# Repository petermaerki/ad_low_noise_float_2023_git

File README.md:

# ad_low_noise_float_2023_git

Ad converter hardware connecting to USB. Used to measure low frequency noise.

* [Instructions (PDF)](instructions/20250919b_instructions_ad_low_noise_float_2023.pdf)
* [Labber Driver (git repo)](https://github.com/nanophysics/labber_ad_low_noise_float_2023)

## Relations between the different software packags

```mermaid
architecture-beta
    group hw(cloud)[Hardware]
    group api(cloud)[API]
    group app(cloud)[Application]

    service pcb(internet)[HardwarePcb] in hw
    service decoder(cloud)[Decoder] in api
    service ad(cloud)[Ad] in api
    service pymeas(server)[Pymeas] in app
    service labber(server)[Labber] in app

    ad:T <--> B:pcb
    decoder:L <-- R:ad
    ad:B <-- T:pymeas
    ad:B <-- T:labber
```

* PCB: The hardware (PCB)
  * https://github.com/petermaerki/ad_low_noise_float_2023_git
  * Directory `hardware` KiCad
  * Directory `software/pico` C++

* Decoder: python package: The protocol decoder written in C++/pybind11
  * https://github.com/petermaerki/ad_low_noise_float_2023_git
  * Directory `software/decoder`

* Ad: python package: The logic to communicate with the PCB
  * https://github.com/petermaerki/ad_low_noise_float_2023_git
  * Directory `src/ad_low_noise_float_2023`

* Labber: The Labber driver written in python
  * https://github.com/nanophysics/labber_ad_low_noise_float_2023

* Pymeas: python application
  * https://github.com/nanophysics/pymeas2019_noise

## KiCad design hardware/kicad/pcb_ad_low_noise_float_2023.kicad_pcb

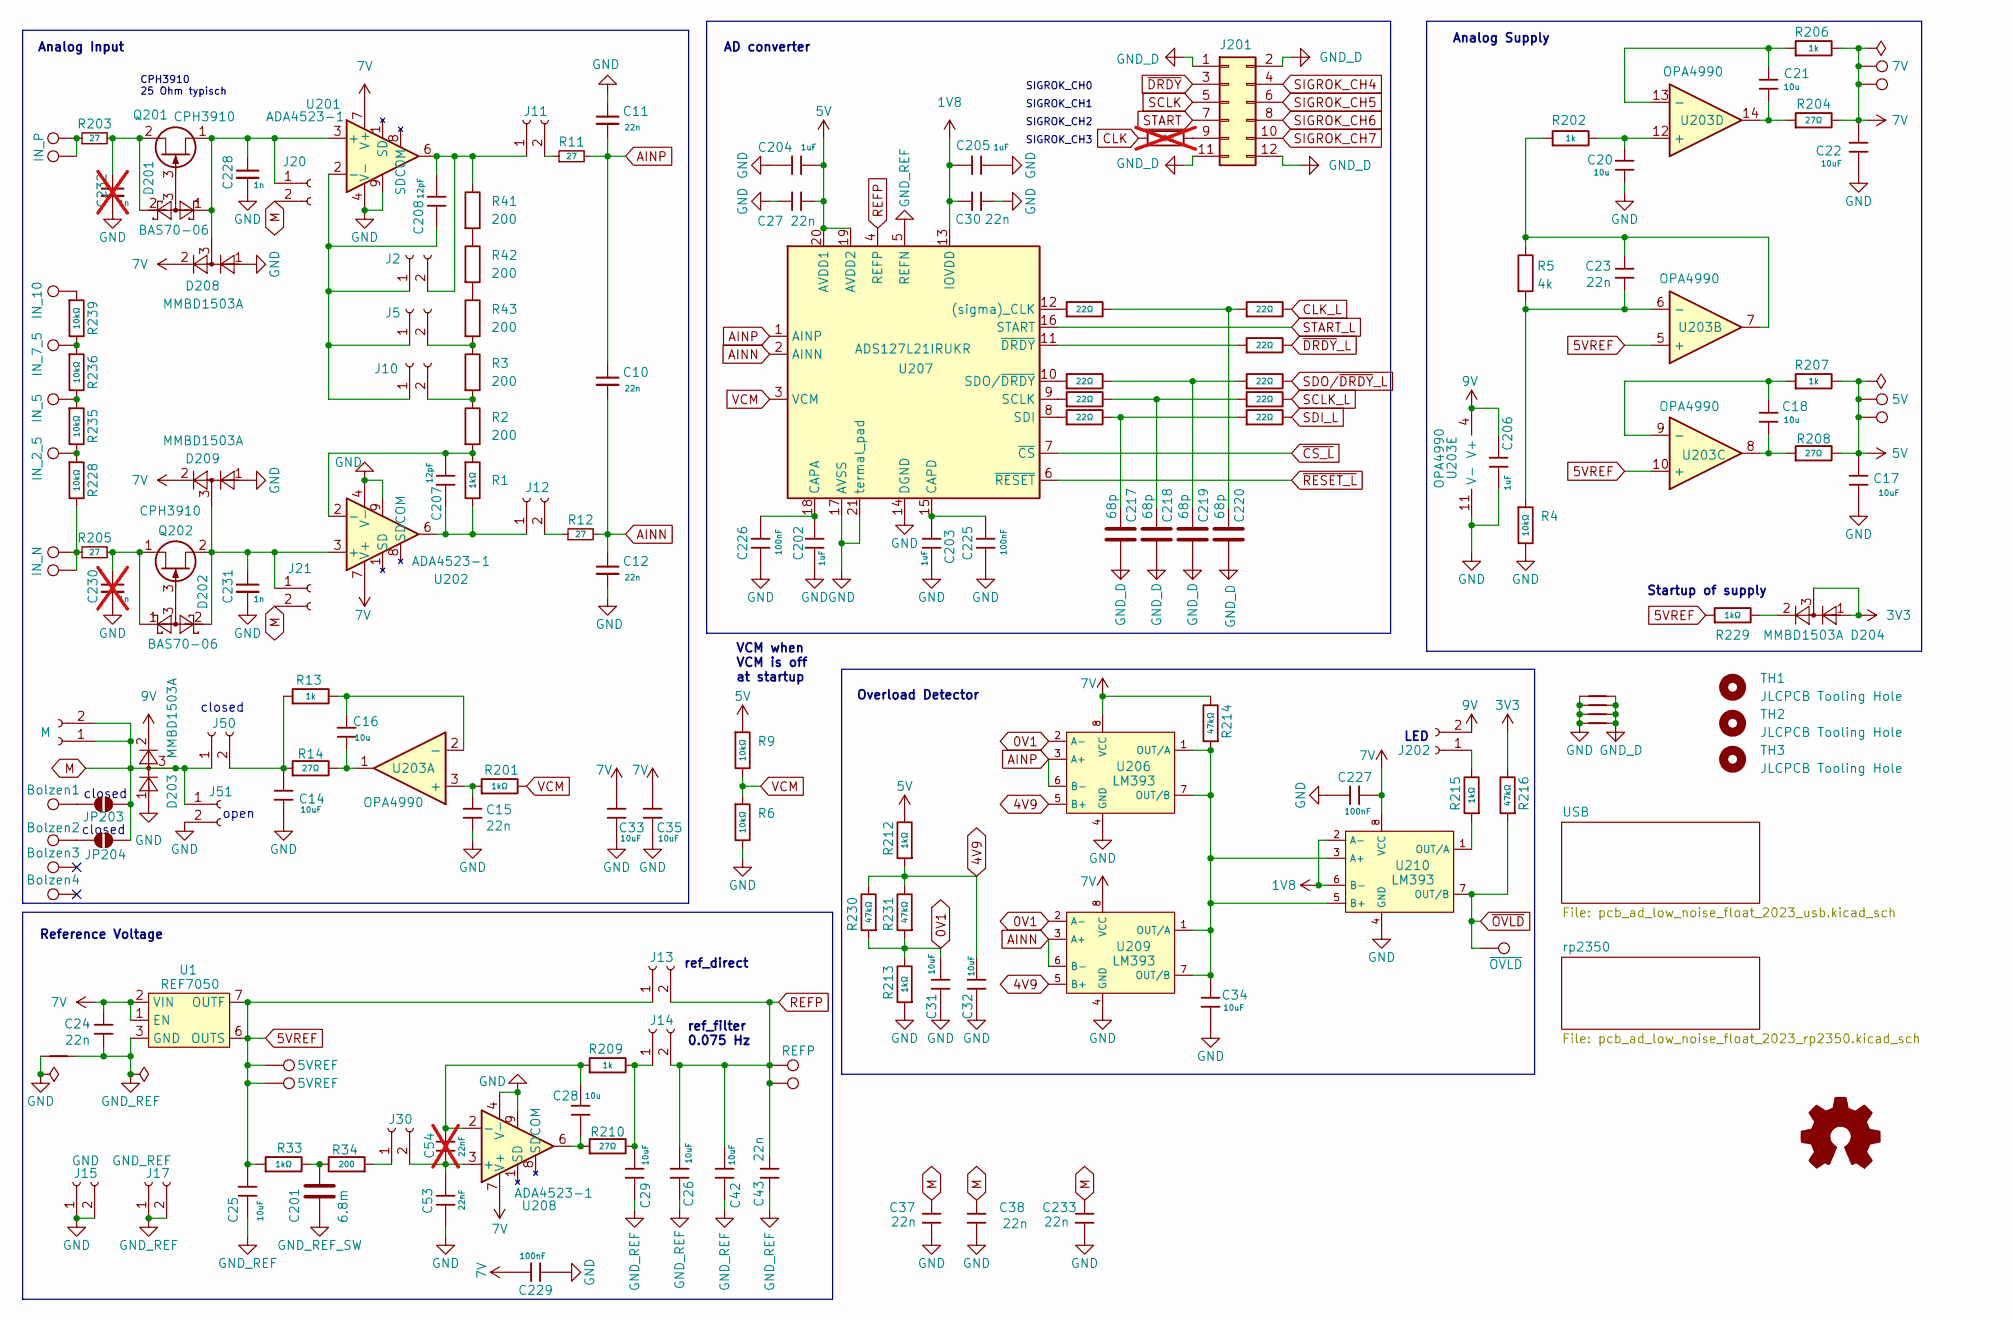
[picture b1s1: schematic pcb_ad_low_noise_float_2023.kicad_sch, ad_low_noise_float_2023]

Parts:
C10, C11, C12: 22n; C_0805; LCSC C77069
C14: 10uF; C_0805; Voltage Rated 50V; Tolerance ±10%; Part GRM21BR61H106KE43L; LCSC C440198
C15, C23, C24, C27, C30, C37, C38, C43, C233: 22n; C_0805; JLC C77069
C16, C18, C20, C21: 10u; C_0805; JLCPCB C440198
C17, C22, C25, C26, C29, C31, C32, C33, C34, C35, C42: 10uF; C_0805; Voltage Rated 50V; Tolerance ±10%; Part GRM21BR61H106KE43L; JLC C440198
C28: 10u; C_0805; Voltage Rated 50V; Tolerance ±10%; Part GRM21BR61H106KE43L; LCSC C440198
C53: 22nF; C_0805; LCSC C77069
C54: 22nF; C_0805; JLC C77069; not fitted
C201: 6.8m; CP_Radial_D18.0mm_P7.50mm_flach_unten
C202, C203, C204, C205, C206: 1uF; C_0805; Voltage Rated 50V; Tolerance ±10%; Part CL21B105KBFNNNE; LCSC C28323
C207, C208: 12pF; C_0805; Voltage Rated 50V; Tolerance ±5%; Part 0805CG120J500NT; LCSC C1792
C217, C218, C219, C220: 68p; C_0402_1005Metric
C225, C226, C227, C229: 100nF; C_0402; Voltage Rated 50V; Tolerance ±10%; Part CL05B104KB54PNC; LCSC C307331
C228, C231: 1n; C_0805; LCSC C46653
C230, C232: 1n; C_0805; LCSC C46653; not fitted
D201, D202: BAS70-06; SOT-23; JLC C22466364
D203, D204, D208, D209: MMBD1503A; SOT-23
IN_N201, IN_N202: IN_N; octoprobe_breakout_PB
IN_N203: IN_2_5; octoprobe_breakout_PB
IN_N204: IN_5; octoprobe_breakout_PB
IN_N205: IN_7_5; octoprobe_breakout_PB
IN_N206: IN_10; octoprobe_breakout_PB
IN_P201, IN_P213: IN_P; octoprobe_breakout_PB
IN_P202, IN_P214: 5V; octoprobe_breakout_PB
IN_P203, IN_P215: 7V; octoprobe_breakout_PB
IN_P206: ~{OVLD}; TestPoint_THTPad_2.0x2.0mm_Drill1.0mm
IN_P208, IN_P212: 5VREF; octoprobe_breakout_PB
IN_P209, IN_P216: REFP; octoprobe_breakout_PB
J2, J5, J10, J11, J12, J13, J14, J20, J21, J30, J50, J51: Conn_01x02_Socket; stiftenleiste_bruecke
J15: GND; stiftenleiste_bruecke
J16: M; stiftenleiste_bruecke
J17: GND_REF; stiftenleiste_bruecke
J201: Conn_02x06_Odd_Even; PinHeader_2x06_P2.54mm_Vertical
J202: stiftenleiste_bruecke
JP203, JP204: SolderJumper_2_Open; SolderJumper-2_P1.3mm_Open_RoundedPad1.0x1.5mm
Logo_open_hardware101: Logo_Open_Hardware_Small; OSHW-Logo2_9.8x8mm_SilkScreen
NT201, NT202, NT203: NetTie_project; NetTie-2_Peter
NT204: NetTie_project; NetTie-2_Peter_wide_back
NT205: NetTie_project; NetTie-2_SMD_Pad0.5mm
Q201, Q202: CPH3910; SOT-23; JLC C480726
R1, R33, R201, R212, R213, R215, R229: 1kΩ; R_0805; JLC C110774
R2, R3, R41, R42, R43: 200; C_0805_2012Metric_Pad1.18x1.45mm_HandSolder; JLC C218416
R4, R228, R235, R236, R239: 10kΩ; R_0805; JLCPCB C509088
R5: 4k; C_0805_2012Metric_Pad1.18x1.45mm_HandSolder; JLC C2828855
R6, R9: 10kΩ; R_0805; Overload Voltage (Max) 150V; Tolerance ±1%; Part 0805W8F1002T5E; JLC C110775
R11, R12, R203, R205: 27; R_0805; LCSC C17594
R13, R202, R206, R207, R209: 1k; R_0805; JLC C110774
R14, R204, R208, R210: 27Ω; R_0805; Overload Voltage (Max) 150V; Tolerance ±1%; Part 0805W8F270JT5E; LCSC C17594
R34: 200; R_0805; JLC C218416
R214, R216, R230, R231: 47kΩ; R_0805; Overload Voltage (Max) 150V; Tolerance ±1%; Part 0805W8F4702T5E; LCSC C17713
R221, R222, R223, R224, R225, R226, R234, R237, R238: 22Ω; R_0402; Overload Voltage (Max) 50V; Tolerance ±1%; Part 0402WGF220JTCE; LCSC C25092
R227: 22Ω; R_0402; Overload Voltage (Max) 50V; Tolerance ±1%; Part 0402WGF220JTCE; LCSC C25092; not fitted
TH1, TH2, TH3: JLCPCB Tooling Hole; JLCPCB_ToolingHole
TP201: Bolzen1; distanzbolz_3
TP202: Bolzen2; distanzbolz_3
TP203: Bolzen3; distanzbolz_3
TP204: Bolzen4; distanzbolz_3
U1: REF7050; Analog_LCC-8_5x5mm_P1.27mm; LCSC C6760318
U201, U202, U208: ADA4523-1; LFCSP-8-1EP_3x3mm_P0.5mm_EP1.6x2.34mm_ThermalVias; JLC C4371130
U203: OPA4990; TSSOP-14_4.4x5mm_P0.65mm; JLC C2862600
U206, U209, U210: LM393; SOIC-8_L5.0-W4.0-P1.27-LS6.0-BL; Supply Voltage 2V~36V;1V~18V; Part LM393DR2G; LCSC C7955
U207: ADS127L21IRUKR; WQFN-20-1EP_3x3mm_P0.4mm_EP1.7x1.7mm_ThermalVias; JLC C20606868

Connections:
0V1: C31.1, R213.2, R230.1, R231.1, U206.2 (A-), U209.2 (A-)
1V8: C30.1, C205.2, U207.13 (IOVDD), U210.2 (A-), U210.6 (B-); also elsewhere on the board
3V3: D204.1, D204.3, R216.2; also elsewhere on the board
4V9: C32.1, R212.1, R230.2, R231.2, U206.5 (B+), U209.5 (B+)
5V: C17.1, C27.2, C204.1, IN_P202.1, IN_P214.1, R9.1, R207.2, R208.2, R212.2, U207.19 (AVDD2), U207.20 (AVDD1)
5VREF: C25.1, IN_P208.1, IN_P212.1, J13.1, R33.1, R229.1, U1.6 (OUTS), U1.7 (OUTF), U203.5 (+), U203.10 (+)
7V: C22.1, C24.1, C33.1, C35.1, C227.1, C229.1, D208.2, D209.2, IN_P203.1, IN_P215.1, R204.2, R206.2, R214.2, U1.1 (EN), U1.2 (VIN), U201.7 (V+), U202.7 (V+), U206.8 (VCC), U208.7 (V+), U209.8 (VCC), U210.8 (VCC)
9V: C206.1, D203.2, J202.2, U203.4 (V+); also elsewhere on the board
AINN: C10.2, C12.1, R12.2, U207.2 (AINN), U209.3 (A+), U209.6 (B-)
AINP: C10.1, C11.2, R11.2, U206.3 (A+), U206.6 (B-), U207.1 (AINP)
CLK: R227.1; also elsewhere on the board
CLK_L: R234.2; also elsewhere on the board
GND: C11.1, C12.2, C14.2, C15.2, C17.2, C20.2, C22.2, C27.1, C30.2, C31.2, C32.2, C33.2, C34.2, C35.2, C37.2, C38.2, C53.2, C202.2, C203.2, C204.2, C205.1, C206.2, C225.2, C226.2, C227.2, C228.2, C229.2, C230.2, C231.2, C232.2, C233.2, D203.1, D208.1, D209.1, J15.1, J15.2, J51.2, NT201.1, NT202.1, NT203.1, NT204.1, NT205.1, R4.2, R6.2, R213.1, U201.4 (V-), U201.9, U202.4 (V-), U202.9, U203.11 (V-), U206.4 (GND), U207.14 (DGND), U207.17 (AVSS), U207.21 (termal_pad), U208.4 (V-), U208.9, U209.4 (GND), U210.4 (GND); also elsewhere on the board
GND_D: C217.2, C218.2, C219.2, C220.2, J201.1, J201.2, J201.11, J201.12, NT202.2, NT203.2, NT204.2, NT205.2; also elsewhere on the board
GND_REF: C24.2, C25.2, C26.2, C29.2, C42.2, C43.2, J17.1, J17.2, NT201.2, U1.3 (GND), U1.4 (GND), U1.5 (GND), U1.8 (GND), U207.5 (REFN); also elsewhere on the board
GND_REF_SW: C201.2; also elsewhere on the board
M: C37.1, C38.1, C233.1, D203.3, J16.1, J16.2, J20.2, J21.2, J50.1, J51.1, JP203.2 (B), JP204.2 (B)
unnamed: C16.2, R14.2, U203.1
unnamed: C18.2, R208.1, U203.8
unnamed: C21.2, R204.1, U203.14
unnamed: C23.1, R5.1, R202.1, U203.7
unnamed: C28.2, R210.1, U208.6
unnamed: C201.1, R33.2, R34.1
unnamed: C217.1, R222.2, R226.1
unnamed: C218.1, R225.2, R238.1
unnamed: C219.1, R224.2, R237.1
unnamed: C220.1, R221.2, R234.1
unnamed: D204.2, R229.2
unnamed: IN_N201.1, IN_N202.1, R205.1, R228.2
unnamed: IN_N203.1, R228.1, R235.2
unnamed: IN_N204.1, R235.1, R236.2
unnamed: IN_N205.1, R236.1, R239.2
unnamed: IN_N206.1, R239.1
unnamed: IN_P201.1, IN_P213.1, R203.1
unnamed: J5.2, R3.1, R43.2
unnamed: C208.2, J2.1, J5.1, J10.1, U201.2 (-)
unnamed: J10.2, R2.1, R3.2
unnamed: C208.1, J2.2, J11.1, R41.1, U201.6
unnamed: J11.2, R11.1
unnamed: C207.2, J12.1, R1.2, U202.6
unnamed: J12.2, R12.1
unnamed: C29.1, J14.1, R209.2, R210.2
unnamed: C228.1, D201.1, D208.3, J20.1, Q201.1 (S), U201.3 (+)
unnamed: C231.1, D202.2, D209.3, J21.1, Q202.2 (D), U202.3 (+)
unnamed: J30.1, R34.2
unnamed: C53.1, C54.1, J30.2, U208.3 (+)
unnamed: C14.1, J50.2, R13.1, R14.1
unnamed: J201.9, R227.2
unnamed: J202.1, R215.2
unnamed: JP203.1 (A), TP201.1
unnamed: JP204.1 (A), TP202.1
unnamed: C232.1, D201.2, Q201.2 (D), R203.2
unnamed: D201.3, Q201.3 (G)
unnamed: D202.3, Q202.3 (G)
unnamed: C230.1, D202.1, Q202.1 (S), R205.2
unnamed: R41.2, R42.1
unnamed: R42.2, R43.1
unnamed: C207.1, R1.1, R2.2, U202.2 (-)
unnamed: C15.1, R201.1, U203.3 (+)
unnamed: C16.1, R13.2, U203.2 (-)
unnamed: C23.2, R4.1, R5.2, U203.6 (-)
unnamed: C18.1, R207.1, U203.9 (-)
unnamed: C20.1, R202.2, U203.12 (+)
unnamed: C21.1, R206.1, U203.13 (-)
unnamed: C34.1, R214.1, U206.1 (OUT/A), U206.7 (OUT/B), U209.1 (OUT/A), U209.7 (OUT/B), U210.3 (A+), U210.5 (B+)
unnamed: R221.1, U207.12 ((sigma)_CLK)
unnamed: C202.1, C226.1, U207.18 (CAPA)
unnamed: C203.1, C225.1, U207.15 (CAPD)
unnamed: R225.1, U207.9 (SCLK)
unnamed: R222.1, U207.8 (SDI)
unnamed: R224.1, U207.10 (SDO/~DRDY)
unnamed: R223.1, U207.11 (~DRDY)
unnamed: C28.1, C54.2, R209.1, U208.2 (-)
unnamed: R215.1, U210.1 (OUT/A)
REFP: C26.1, C42.1, C43.1, IN_P209.1, IN_P216.1, J13.2, J14.2, U207.4 (REFP)
SCLK: J201.5; also elsewhere on the board
SCLK_L: R238.2; also elsewhere on the board
SDI_L: R226.2; also elsewhere on the board
SDO/~DRDY_L: R237.2; also elsewhere on the board
SIGROK_CH4: J201.4; also elsewhere on the board
SIGROK_CH5: J201.6; also elsewhere on the board
SIGROK_CH6: J201.8; also elsewhere on the board
SIGROK_CH7: J201.10; also elsewhere on the board
START: J201.7; also elsewhere on the board
START_L: U207.16 (START); also elsewhere on the board
VCM: R6.1, R9.2, R201.2, U207.3 (VCM)
~CS_L: U207.7 (~CS); also elsewhere on the board
~DRDY: J201.3; also elsewhere on the board
~DRDY_L: R223.2; also elsewhere on the board
~OVLD: IN_P206.1, R216.1, U210.7 (OUT/B); also elsewhere on the board
~RESET_L: U207.6 (~RESET); also elsewhere on the board

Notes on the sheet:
SIGROK_CH1
SIGROK_CH2
ref_filter 0.075 Hz
closed
LED
Reference Voltage
Overload Detector
open
Startup of supply
AD converter
CPH3910 25 Ohm typisch
ref_direct
VCM when VCM is off at startup
SIGROK_CH0
Analog Input
SIGROK_CH3
Analog Supply

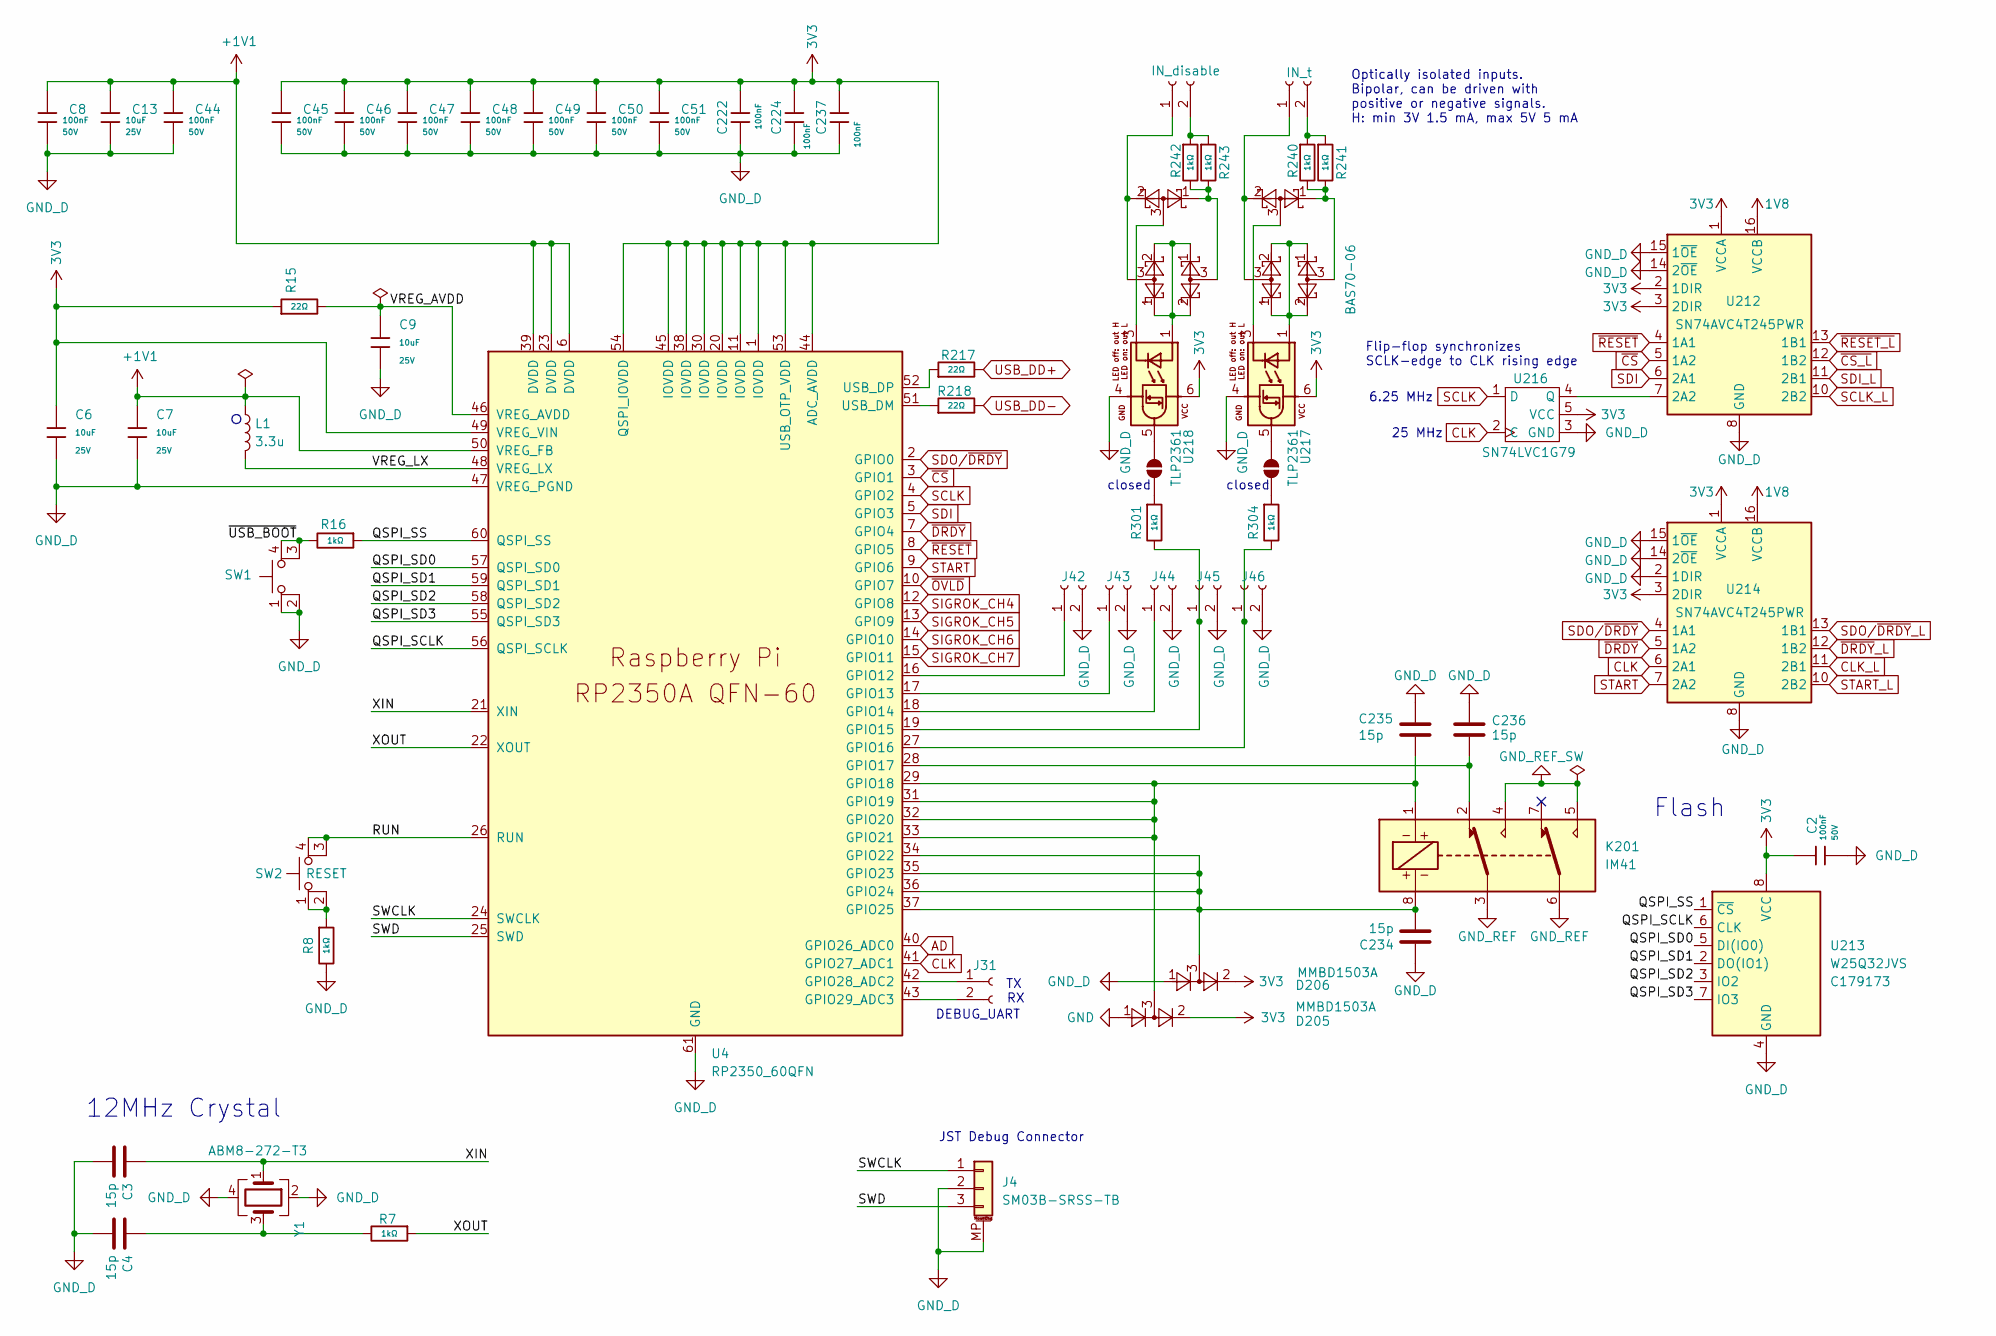
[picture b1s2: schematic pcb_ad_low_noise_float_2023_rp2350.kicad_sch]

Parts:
C2, C8, C44, C45, C46, C47, C48, C49, C50, C51, C222, C224, C237: 100nF; C_0402; Voltage Rated 50V; Tolerance ±10%; Part CL05B104KB54PNC; LCSC C307331
C3, C4, C234, C235, C236: 15p; C_0402_1005Metric
C6, C7, C9, C13: 10uF; C_0603; Voltage Rated 25V; Tolerance ±20%; Part CL10A106MA8NRNC; LCSC C96446
D205, D206: MMBD1503A; SOT-23
D210, D211, D212, D213, D214, D215: BAS70-06; SOT-23; JLC C22466364
J4: SM03B-SRSS-TB; JST_SH_SM03B-SRSS-TB_1x03-1MP_P1.00mm_Horizontal; JLC C160403
J31, J42, J43, J44, J45, J46: Conn_01x02_Socket; stiftenleiste_bruecke
J401: IN_t; stiftenleiste_bruecke
J402: IN_disable; stiftenleiste_bruecke
JP205, JP206: SolderJumper_2_Open; SolderJumper-2_P1.3mm_Open_RoundedPad1.0x1.5mm
K201: IM41; Relay_2P2T_10x6mm_TE_IMxxG; JLCPCB C377684
L1: 3.3u; L_pol_2016; JLC C42411119
R7, R8, R16, R240, R241, R242, R243, R301, R304: 1kΩ; R_0805; JLC C110774
R15, R217, R218: 22Ω; R_0402; Overload Voltage (Max) 50V; Tolerance ±1%; Part 0402WGF220JTCE; LCSC C25092
SW1, SW2: SW_MEC_5E; SW_TS-1187A-B-A-B; JLC C318884
U4: RP2350_60QFN; RP2350-QFN-60-1EP_7x7_P0.4mm_EP3.4x3.4mm_ThermalVias; JLC C42411118
U212, U214: SN74AVC4T245PWR; TSSOP-16_4.4x5mm_P0.65mm
U213: W25Q32JVS; SOIC-8_5.23x5.23mm_P1.27mm; JLC C179173
U216: SN74LVC1G79; SOT-23-5; JLCPCB C42878
U217, U218: TLP2361; SO-5-6_4.55x3.7mm_P1.27mm; JLCPCB C107626
Y1: ABM8-272-T3; Crystal_SMD_3225-4Pin_3.2x2.5mm; JLC C20625731

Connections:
1V8: U212.16 (VCCB), U214.16 (VCCB); also elsewhere on the board
3V3: C2.1, C6.1, C45.1, C46.1, C47.1, C48.1, C49.1, C50.1, C51.1, C222.1, C224.1, C237.1, D205.2, D206.2, R15.1, U4.1 (IOVDD), U4.11 (IOVDD), U4.20 (IOVDD), U4.30 (IOVDD), U4.38 (IOVDD), U4.44 (ADC_AVDD), U4.45 (IOVDD), U4.49 (VREG_VIN), U4.53 (USB_OTP_VDD), U4.54 (QSPI_IOVDD), U212.1 (VCCA), U212.2 (1DIR), U212.3 (2DIR), U213.8 (VCC), U214.1 (VCCA), U214.3 (2DIR), U216.5 (VCC), U217.6 (VDD), U218.6 (VDD); also elsewhere on the board
+1V1: C7.1, C8.1, C13.1, C44.1, L1.1, U4.6 (DVDD), U4.23 (DVDD), U4.39 (DVDD), U4.50 (VREG_FB)
/rp2350/QSPI_SCLK: U4.56 (QSPI_SCLK), U213.6 (CLK)
/rp2350/QSPI_SD0: U4.57 (QSPI_SD0), U213.5 (DI(IO0))
/rp2350/QSPI_SD1: U4.59 (QSPI_SD1), U213.2 (DO(IO1))
/rp2350/QSPI_SD2: U4.58 (QSPI_SD2), U213.3 (IO2)
/rp2350/QSPI_SD3: U4.55 (QSPI_SD3), U213.7 (IO3)
/rp2350/QSPI_SS: R16.1, U4.60 (QSPI_SS), U213.1 (~CS)
/rp2350/RUN: SW2.3 (K), SW2.4 (A), U4.26 (RUN)
/rp2350/SWCLK: J4.1, U4.24 (SWCLK)
/rp2350/SWD: J4.3, U4.25 (SWD)
/rp2350/VREG_AVDD: C9.1, R15.2, U4.46 (VREG_AVDD)
/rp2350/VREG_LX: L1.2, U4.48 (VREG_LX)
/rp2350/XIN: C3.1, U4.21 (XIN), Y1.1
/rp2350/XOUT: R7.1, U4.22 (XOUT)
AD: U4.40 (GPIO26_ADC0); also elsewhere on the board
CLK: U4.41 (GPIO27_ADC1), U214.6 (2A1), U216.2 (C); also elsewhere on the board
CLK_L: U214.11 (2B1); also elsewhere on the board
GND: D205.1; also elsewhere on the board
GND_D: C2.2, C3.2, C4.2, C6.2, C7.2, C8.2, C9.2, C13.2, C44.2, C45.2, C46.2, C47.2, C48.2, C49.2, C50.2, C51.2, C222.2, C224.2, C234.1, C235.1, C236.1, C237.2, D206.1, J4.2, J4.MP (MountPin), J42.2, J43.2, J44.2, J45.2, J46.2, R8.2, SW1.1, SW1.2, U4.47 (VREG_PGND), U4.61 (GND), U212.8 (GND), U212.9 (GND), U212.14 (2~OE), U212.15 (1~OE), U213.4 (GND), U214.2 (1DIR), U214.8 (GND), U214.9 (GND), U214.14 (2~OE), U214.15 (1~OE), U216.3 (GND), U217.4 (GND), U218.4 (GND), Y1.2, Y1.4; also elsewhere on the board
GND_REF: K201.3, K201.6; also elsewhere on the board
GND_REF_SW: K201.4, K201.5; also elsewhere on the board
unnamed: C4.1, R7.2, Y1.3
unnamed: D210.1, D211.3, R240.2, R241.2
unnamed: D214.1, D215.3, R242.2, R243.2
unnamed: J31.1, U4.42 (GPIO28_ADC2)
unnamed: J31.2, U4.43 (GPIO29_ADC3)
unnamed: J42.1, U4.16 (GPIO12)
unnamed: J43.1, U4.17 (GPIO13)
unnamed: J44.1, U4.18 (GPIO14)
unnamed: J45.1, R301.2, U4.19 (GPIO15)
unnamed: J46.1, R304.2, U4.27 (GPIO16)
unnamed: D210.2, D212.3, J401.1
unnamed: J401.2, R240.1, R241.1
unnamed: D213.3, D214.2, J402.1
unnamed: J402.2, R242.1, R243.1
unnamed: JP205.1 (A), U217.5 (VO)
unnamed: JP205.2 (B), R304.1
unnamed: JP206.1 (A), U218.5 (VO)
unnamed: JP206.2 (B), R301.1
unnamed: R8.1, SW2.1, SW2.2
unnamed: R16.2, SW1.3 (K), SW1.4 (A)
unnamed: C236.2, K201.2, U4.28 (GPIO17)
unnamed: C235.2, D205.3, K201.1, U4.29 (GPIO18), U4.31 (GPIO19), U4.32 (GPIO20), U4.33 (GPIO21)
unnamed: C234.2, D206.3, K201.8, U4.34 (GPIO22), U4.35 (GPIO23), U4.36 (GPIO24), U4.37 (GPIO25)
unnamed: R218.1, U4.51 (USB_DM)
unnamed: R217.1, U4.52 (USB_DP)
unnamed: U212.7 (2A2), U216.4 (Q)
unnamed: D211.1, D211.2, D212.1, D212.2, U217.1 (A)
unnamed: D210.3, U217.3 (K)
unnamed: D213.1, D213.2, D215.1, D215.2, U218.1 (A)
unnamed: D214.3, U218.3 (K)
SCLK: U4.4 (GPIO2), U216.1 (D); also elsewhere on the board
SCLK_L: U212.10 (2B2); also elsewhere on the board
SDI: U4.5 (GPIO3), U212.6 (2A1)
SDI_L: U212.11 (2B1); also elsewhere on the board
SDO/~DRDY: U4.2 (GPIO0), U214.4 (1A1)
SDO/~DRDY_L: U214.13 (1B1); also elsewhere on the board
SIGROK_CH4: U4.12 (GPIO8); also elsewhere on the board
SIGROK_CH5: U4.13 (GPIO9); also elsewhere on the board
SIGROK_CH6: U4.14 (GPIO10); also elsewhere on the board
SIGROK_CH7: U4.15 (GPIO11); also elsewhere on the board
START: U4.9 (GPIO6), U214.7 (2A2); also elsewhere on the board
START_L: U214.10 (2B2); also elsewhere on the board
USB_DD+: R217.2; also elsewhere on the board
USB_DD-: R218.2; also elsewhere on the board
~CS_L: U212.12 (1B2); also elsewhere on the board
~CS: U4.3 (GPIO1), U212.5 (1A2)
~DRDY: U4.7 (GPIO4), U214.5 (1A2); also elsewhere on the board
~DRDY_L: U214.12 (1B2); also elsewhere on the board
~OVLD: U4.10 (GPIO7); also elsewhere on the board
~RESET_L: U212.13 (1B1); also elsewhere on the board
~RESET: U4.8 (GPIO5), U212.4 (1A1)

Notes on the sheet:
DEBUG_UART
12MHz Crystal
closed
25 MHz
JST Debug Connector
Flip-flop synchronizes SCLK-edge to CLK rising edge
6.25 MHz
Optically isolated inputs. Bipolar, can be driven with positive or negative signals. H: min 3V 1.5 mA, max 5V 5 mA
Flash

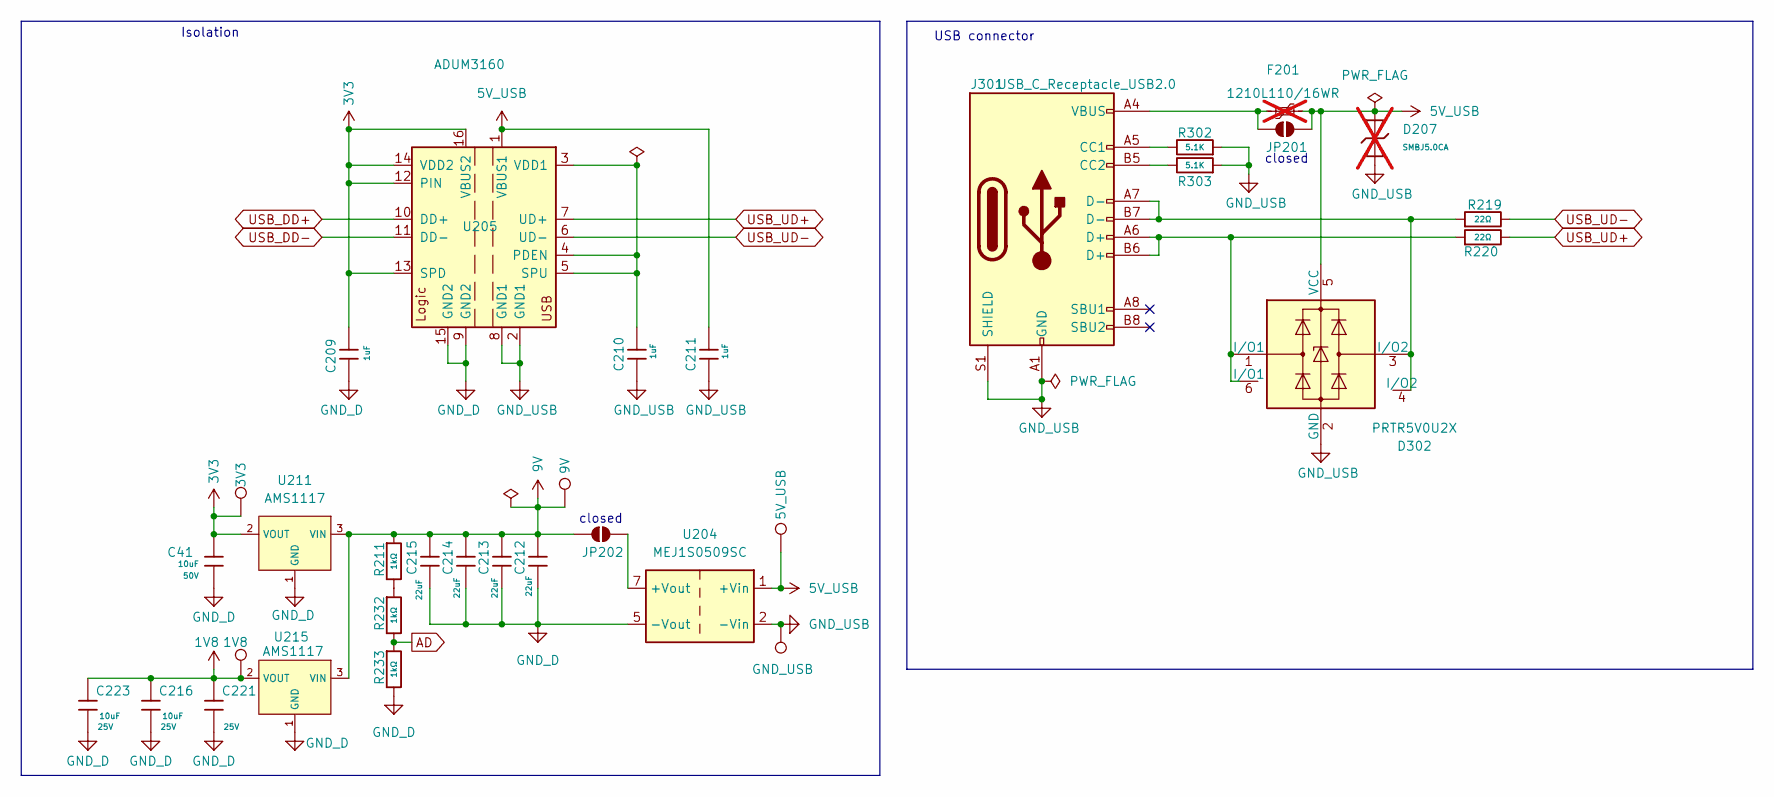
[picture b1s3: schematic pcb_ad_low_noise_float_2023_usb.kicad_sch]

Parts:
C41: 10uF; C_0805; Voltage Rated 50V; Tolerance ±10%; Part GRM21BR61H106KE43L; JLC C440198
C209, C210, C211: 1uF; C_0805; Voltage Rated 50V; Tolerance ±10%; Part CL21B105KBFNNNE; LCSC C28323
C212, C213, C214, C215: 22uF; C_1206; Voltage Rated 25V; Part CL31A226KAHNNNE; LCSC C12891
C216, C221, C223: 10uF; C_0603; Voltage Rated 25V; Tolerance ±20%; Part CL10A106MA8NRNC; LCSC C96446
D207: SMBJ5.0CA; D_SMB; Part SMBJ5.0CA; LCSC C19077559; not fitted
D302: PRTR5V0U2X; Texas_USON-6_1x1.45mm_P0.5mm_SMD; JLC C2937001
F201: 1210L110/16WR; Fuse_1210_3225Metric_Pad1.42x2.65mm_HandSolder; JLCPCB C720185; not fitted
IN_P204: 9V; octoprobe_breakout_PB
IN_P205: 3V3; octoprobe_breakout_PB
IN_P207: 5V_USB; TestPoint_THTPad_2.0x2.0mm_Drill1.0mm
IN_P210: GND_USB; TestPoint_THTPad_2.0x2.0mm_Drill1.0mm
IN_P211: 1V8; octoprobe_breakout_PB
J301: USB_C_Receptacle_USB2.0; USB_C_Receptacle_Palconn_UTC16-G; JLC C165948
JP201, JP202: SolderJumper_2_Open; SolderJumper-2_P1.3mm_Open_RoundedPad1.0x1.5mm
R211, R232, R233: 1kΩ; R_0805; JLC C110774
R219, R220: 22Ω; R_0402; Overload Voltage (Max) 50V; Tolerance ±1%; Part 0402WGF220JTCE; LCSC C25092
R302, R303: 5.1K; R_0402_1005Metric
U204: MEJ1S0509SC; Converter_DCDC
U205: ADUM3160; SOIC-16W_7.5x10.3mm_P1.27mm; JLC C284149
U211: AMS1117; SOT-223-3_TabPin2; Output Voltage 3.3V; Dropout Voltage 1.3V@(800mA); Part AMS1117-3.3; LCSC C6186
U215: AMS1117; SOT-223-3_TabPin2; LCSC C6185

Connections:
1V8: C216.1, C221.1, C223.1, IN_P211.1, U215.2 (VOUT); also elsewhere on the board
3V3: C41.1, C209.1, IN_P205.1, U205.12 (PIN), U205.13 (SPD), U205.14 (VDD2), U205.16 (VBUS2), U211.2 (VOUT); also elsewhere on the board
5V_USB: C211.1, D207.2, D302.5 (VCC), F201.2, IN_P207.1, JP201.2 (B), U204.1 (+Vin), U205.1 (VBUS1)
9V: C212.1, C213.1, C214.1, C215.1, IN_P204.1, JP202.1 (A), R211.1, U211.3 (VIN), U215.3 (VIN); also elsewhere on the board
AD: R232.2, R233.1; also elsewhere on the board
GND_D: C41.2, C209.2, C212.2, C213.2, C214.2, C215.2, C216.2, C221.2, C223.2, R233.2, U204.5 (-Vout), U205.9 (GND2), U205.15 (GND2), U211.1 (GND), U215.1 (GND); also elsewhere on the board
GND_USB: C210.2, C211.2, D207.1, D302.2 (GND), IN_P210.1, J301.A1 (GND), J301.A12 (GND), J301.B1 (GND), J301.B12 (GND), J301.S1 (SHIELD), R302.2, R303.2, U204.2 (-Vin), U205.2 (GND1), U205.8 (GND1)
unnamed: D302.1 (I/O1), D302.6 (I/O1), J301.A6 (D+), J301.B6 (D+), R220.1
unnamed: D302.3 (I/O2), D302.4 (I/O2), J301.A7 (D-), J301.B7 (D-), R219.1
unnamed: J301.A5 (CC1), R302.1
unnamed: J301.B5 (CC2), R303.1
unnamed: F201.1, J301.A4 (VBUS), J301.A9 (VBUS), J301.B4 (VBUS), J301.B9 (VBUS), JP201.1 (A)
unnamed: JP202.2 (B), U204.7 (+Vout)
unnamed: R211.2, R232.1
unnamed: C210.1, U205.3 (VDD1), U205.4 (PDEN), U205.5 (SPU)
USB_DD+: U205.10 (DD+); also elsewhere on the board
USB_DD-: U205.11 (DD-); also elsewhere on the board
USB_UD+: R220.2, U205.7 (UD+)
USB_UD-: R219.2, U205.6 (UD-)

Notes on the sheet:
closed
USB connector
Isolation

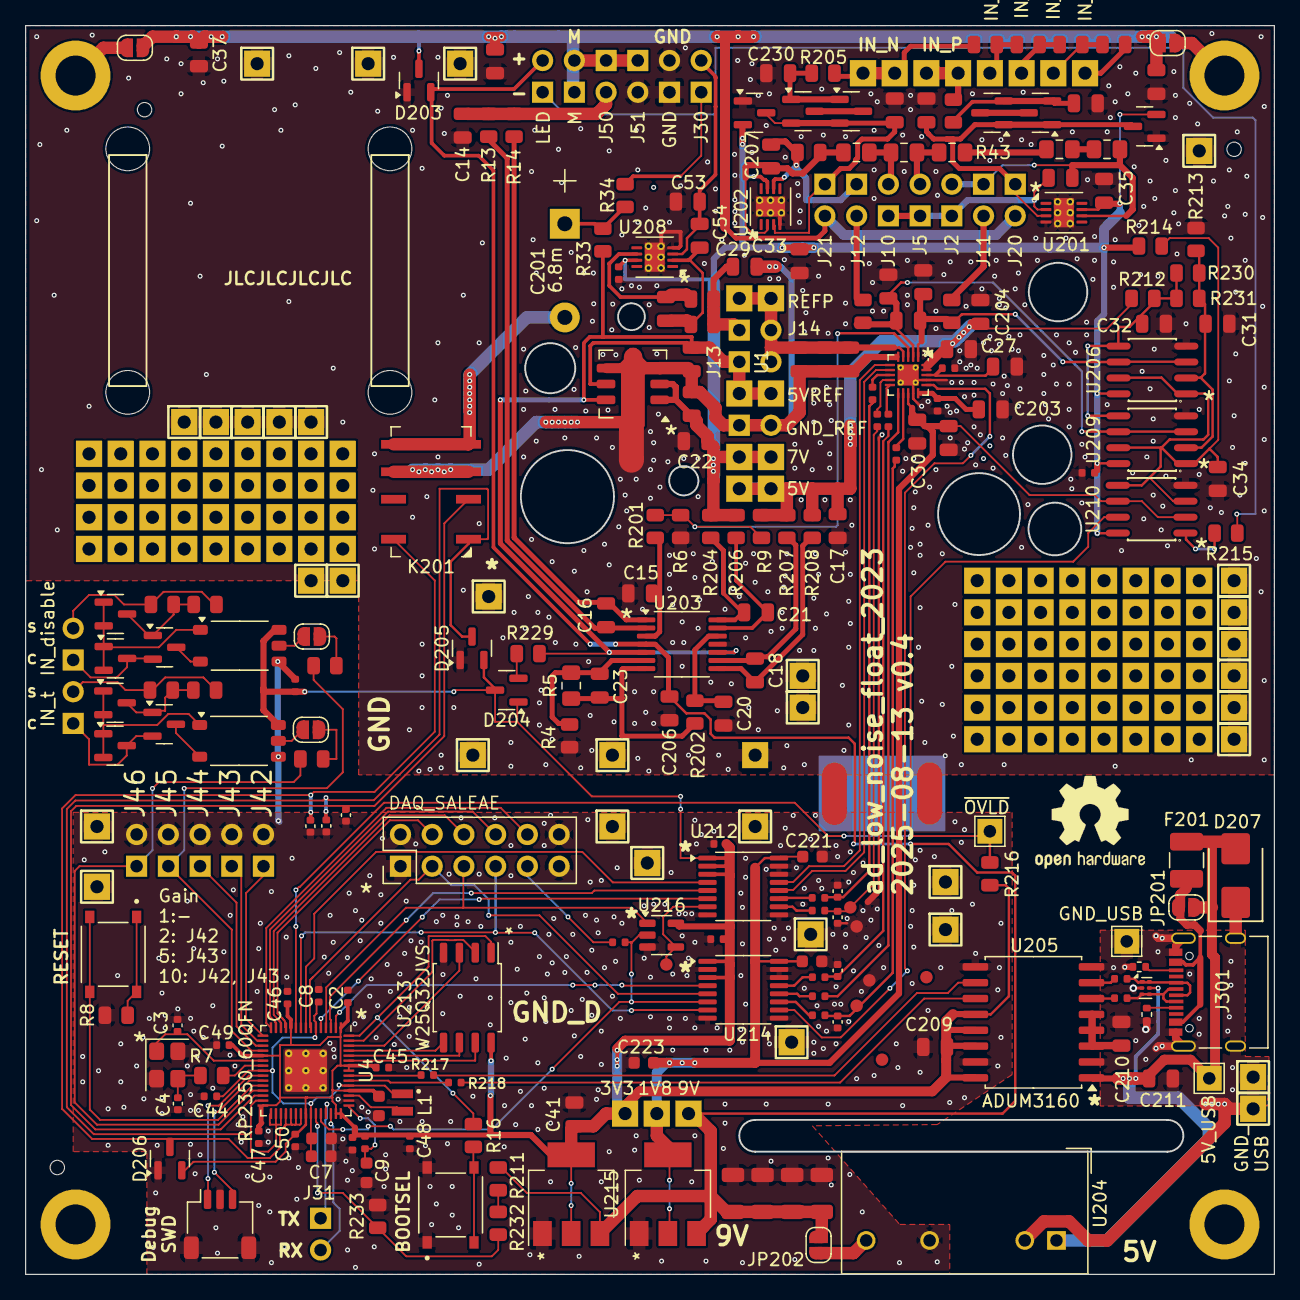
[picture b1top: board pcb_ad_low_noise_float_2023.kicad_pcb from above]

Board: 2 copper layers, 100.0 x 100.0 mm, 263 parts (0 on the bottom side), 154 nets.

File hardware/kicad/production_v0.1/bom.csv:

Designator,Footprint,Quantity,Value,LCSC Part #
"C10, C11, C12, C15, C16, C19, C20, C23, C24, C27, C30, C37, C38, C39, C40, C43",C_0805,16,22n,C77069
"C13, C52, C6, C7, C9",C_0603,5,10uF,C96446
"C14, C17, C22, C25, C26, C29, C31, C32, C33, C34, C35, C36, C41, C42",C_0805,14,10uF,C440198
"C18, C21, C28",C_0805,3,100nF,C28233
"C2, C44, C45, C46, C47, C48, C49, C50, C51, C8",C_0402,10,100nF,C307331
"C202, C203, C204, C205, C206, C209, C210, C211, C212",C_0805,9,1uF,C28323
"C207, C208",C_0805,2,12pF,C1792
"C3, C4",0402,2,15p,
"D201, D202",SOT-23,2,BAS70-06,C22466364
D203,SOT-23,1,MMBD1503A,
D302,Texas_USON-6_1x1.45mm_P0.5mm_SMD,1,PRTR5V0U2X,C2937001
IN_N201,TestPoint_THTPad_2.0x2.0mm_Drill1.0mm,1,IN_N,
IN_P201,TestPoint_THTPad_2.0x2.0mm_Drill1.0mm,1,IN_P,
IN_P202,TestPoint_THTPad_2.0x2.0mm_Drill1.0mm,1,5V,
IN_P203,TestPoint_THTPad_2.0x2.0mm_Drill1.0mm,1,7V,
IN_P204,TestPoint_THTPad_2.0x2.0mm_Drill1.0mm,1,9V,
IN_P205,TestPoint_THTPad_2.0x2.0mm_Drill1.0mm,1,3V3,
IN_P206,TestPoint_THTPad_2.0x2.0mm_Drill1.0mm,1,~{OVLD},
IN_P207,TestPoint_THTPad_2.0x2.0mm_Drill1.0mm,1,5V_USB,
IN_P208,TestPoint_THTPad_2.0x2.0mm_Drill1.0mm,1,5VREF,
IN_P209,TestPoint_THTPad_2.0x2.0mm_Drill1.0mm,1,REFP,
IN_P210,TestPoint_THTPad_2.0x2.0mm_Drill1.0mm,1,GND_USB,
"J10, J11, J20, J21, J5",stiftenleiste_bruecke,5,Conn_01x02_Socket,
J301,USB_C_Receptacle_Palconn_UTC16-G,1,USB_C_Receptacle_USB2.0,C165948
J4,JST_SH_SM03B-SRSS-TB_1x03-1MP_P1.00mm_Horizontal,1,SM03B-SRSS-TB,C160403
L1,L_pol_2016,1,3.3u,C42411119
M201,TestPoint_THTPad_2.0x2.0mm_Drill1.0mm,1,M,
"Q201, Q202",SOT-23,2,CPH3910,C480726
"R1, R16, R201, R203, R212, R213, R215, R7, R8",R_0805,9,1kΩ,C110774
"R11, R12",R_0805,2,27,C17594
"R13, R206, R207, R209, R211, R214, R216",R_0805,7,47kΩ,C17713
"R14, R204, R208, R210",R_0805,4,27Ω,C17594
"R15, R217, R218, R219, R220, R221, R222, R223, R224, R225, R226, R227, R228",R_0402,13,22Ω,C25092
"R2, R3, R41, R42, R43",0805,5,200,C218416
"R202, R4",R_0805,2,10kΩ,C17414
R205,R_0805,1,200, C218416
"R302, R303",0402,2,5.1K,
R5,0805,1,4k,C2828855
"SW1, SW2",SW_TS-1187A-B-A-B,2,SW_MEC_5E,C318884
TP201,distanzbolz_3,1,Bolzen1,
TP202,distanzbolz_3,1,Bolzen2,
TP203,distanzbolz_3,1,Bolzen3,
TP204,distanzbolz_3,1,Bolzen4,
U1,Analog_LCC-8_5x5mm_P1.27mm,1,REF7050,C6760318
"U201, U202, U208",LFCSP-8-1EP_3x3mm_P0.5mm_EP1.6x2.34mm_ThermalVias,3,ADA4523-1,C4371130
U203,TSSOP-14_4.4x5mm_P0.65mm,1,OPA4990,C2862600
U205,SOIC-16W_7.5x10.3mm_P1.27mm,1,ADUM3160,C284149
"U206, U209, U210",SOIC-8_L5.0-W4.0-P1.27-LS6.0-BL,3,LM393,C7955
U207,WQFN-20-1EP_3x3mm_P0.4mm_EP1.7x1.7mm_ThermalVias,1,ADS127L21IRUKR,C20606868
U211,SOT-223-3_TabPin2,1,AMS1117,C6186
U213,SOIC-8_5.23x5.23mm_P1.27mm,1,W25Q32JVS,C179173
U4,RP2350-QFN-60-1EP_7x7_P0.4mm_EP3.4x3.4mm_ThermalVias,1,RP2350_60QFN,C42411118
Y1,Crystal_SMD_3225-4Pin_3.2x2.5mm,1,ABM8-272-T3,C20625731

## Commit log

2025-03-12 Vergleich AD
2025-03-12 Add kicad template
2025-11-18 Initial commit
    Update documentation
2025-11-18 squashed history to trash private data
2025-11-18 Mark obsolete actions
2025-11-18 Rename workflows

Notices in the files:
hardware/kicad/pcb_ad_low_noise_float_2023.kicad_pcb:
The MIT License (MIT)
